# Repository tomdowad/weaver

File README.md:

# weaver
A collection of circuit boards and methods in support of reusable modular electronics

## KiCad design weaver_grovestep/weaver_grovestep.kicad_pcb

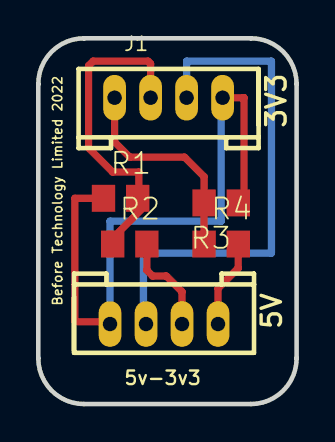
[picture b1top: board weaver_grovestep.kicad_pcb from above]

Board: 2 copper layers, 14.4 x 20.3 mm, 6 parts (0 on the bottom side), 6 nets.

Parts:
J1, J2: 4P-2.0; HW4-2.0
R1, R2, R3, R4: R0805

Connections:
unnamed: J1.2, R1.2, R2.1
unnamed: J1.1, R3.2, R4.1
unnamed: J1.4, J2.4, R1.1, R3.1
unnamed: J1.3, J2.3
unnamed: J2.2, R2.2
unnamed: J2.1, R4.2

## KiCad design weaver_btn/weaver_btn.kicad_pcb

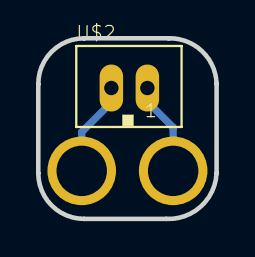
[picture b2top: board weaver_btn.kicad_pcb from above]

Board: 2 copper layers, 9.9 x 10.0 mm, 3 parts (0 on the bottom side), 2 nets.

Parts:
U$1, U$3: BUTTON_PAD
U$2: JST-PH_2-PIN_HEADER; JST_B2B-PH_HEADER

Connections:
unnamed: U$2.P1, U$3.P$1
unnamed: U$1.P$1, U$2.P2

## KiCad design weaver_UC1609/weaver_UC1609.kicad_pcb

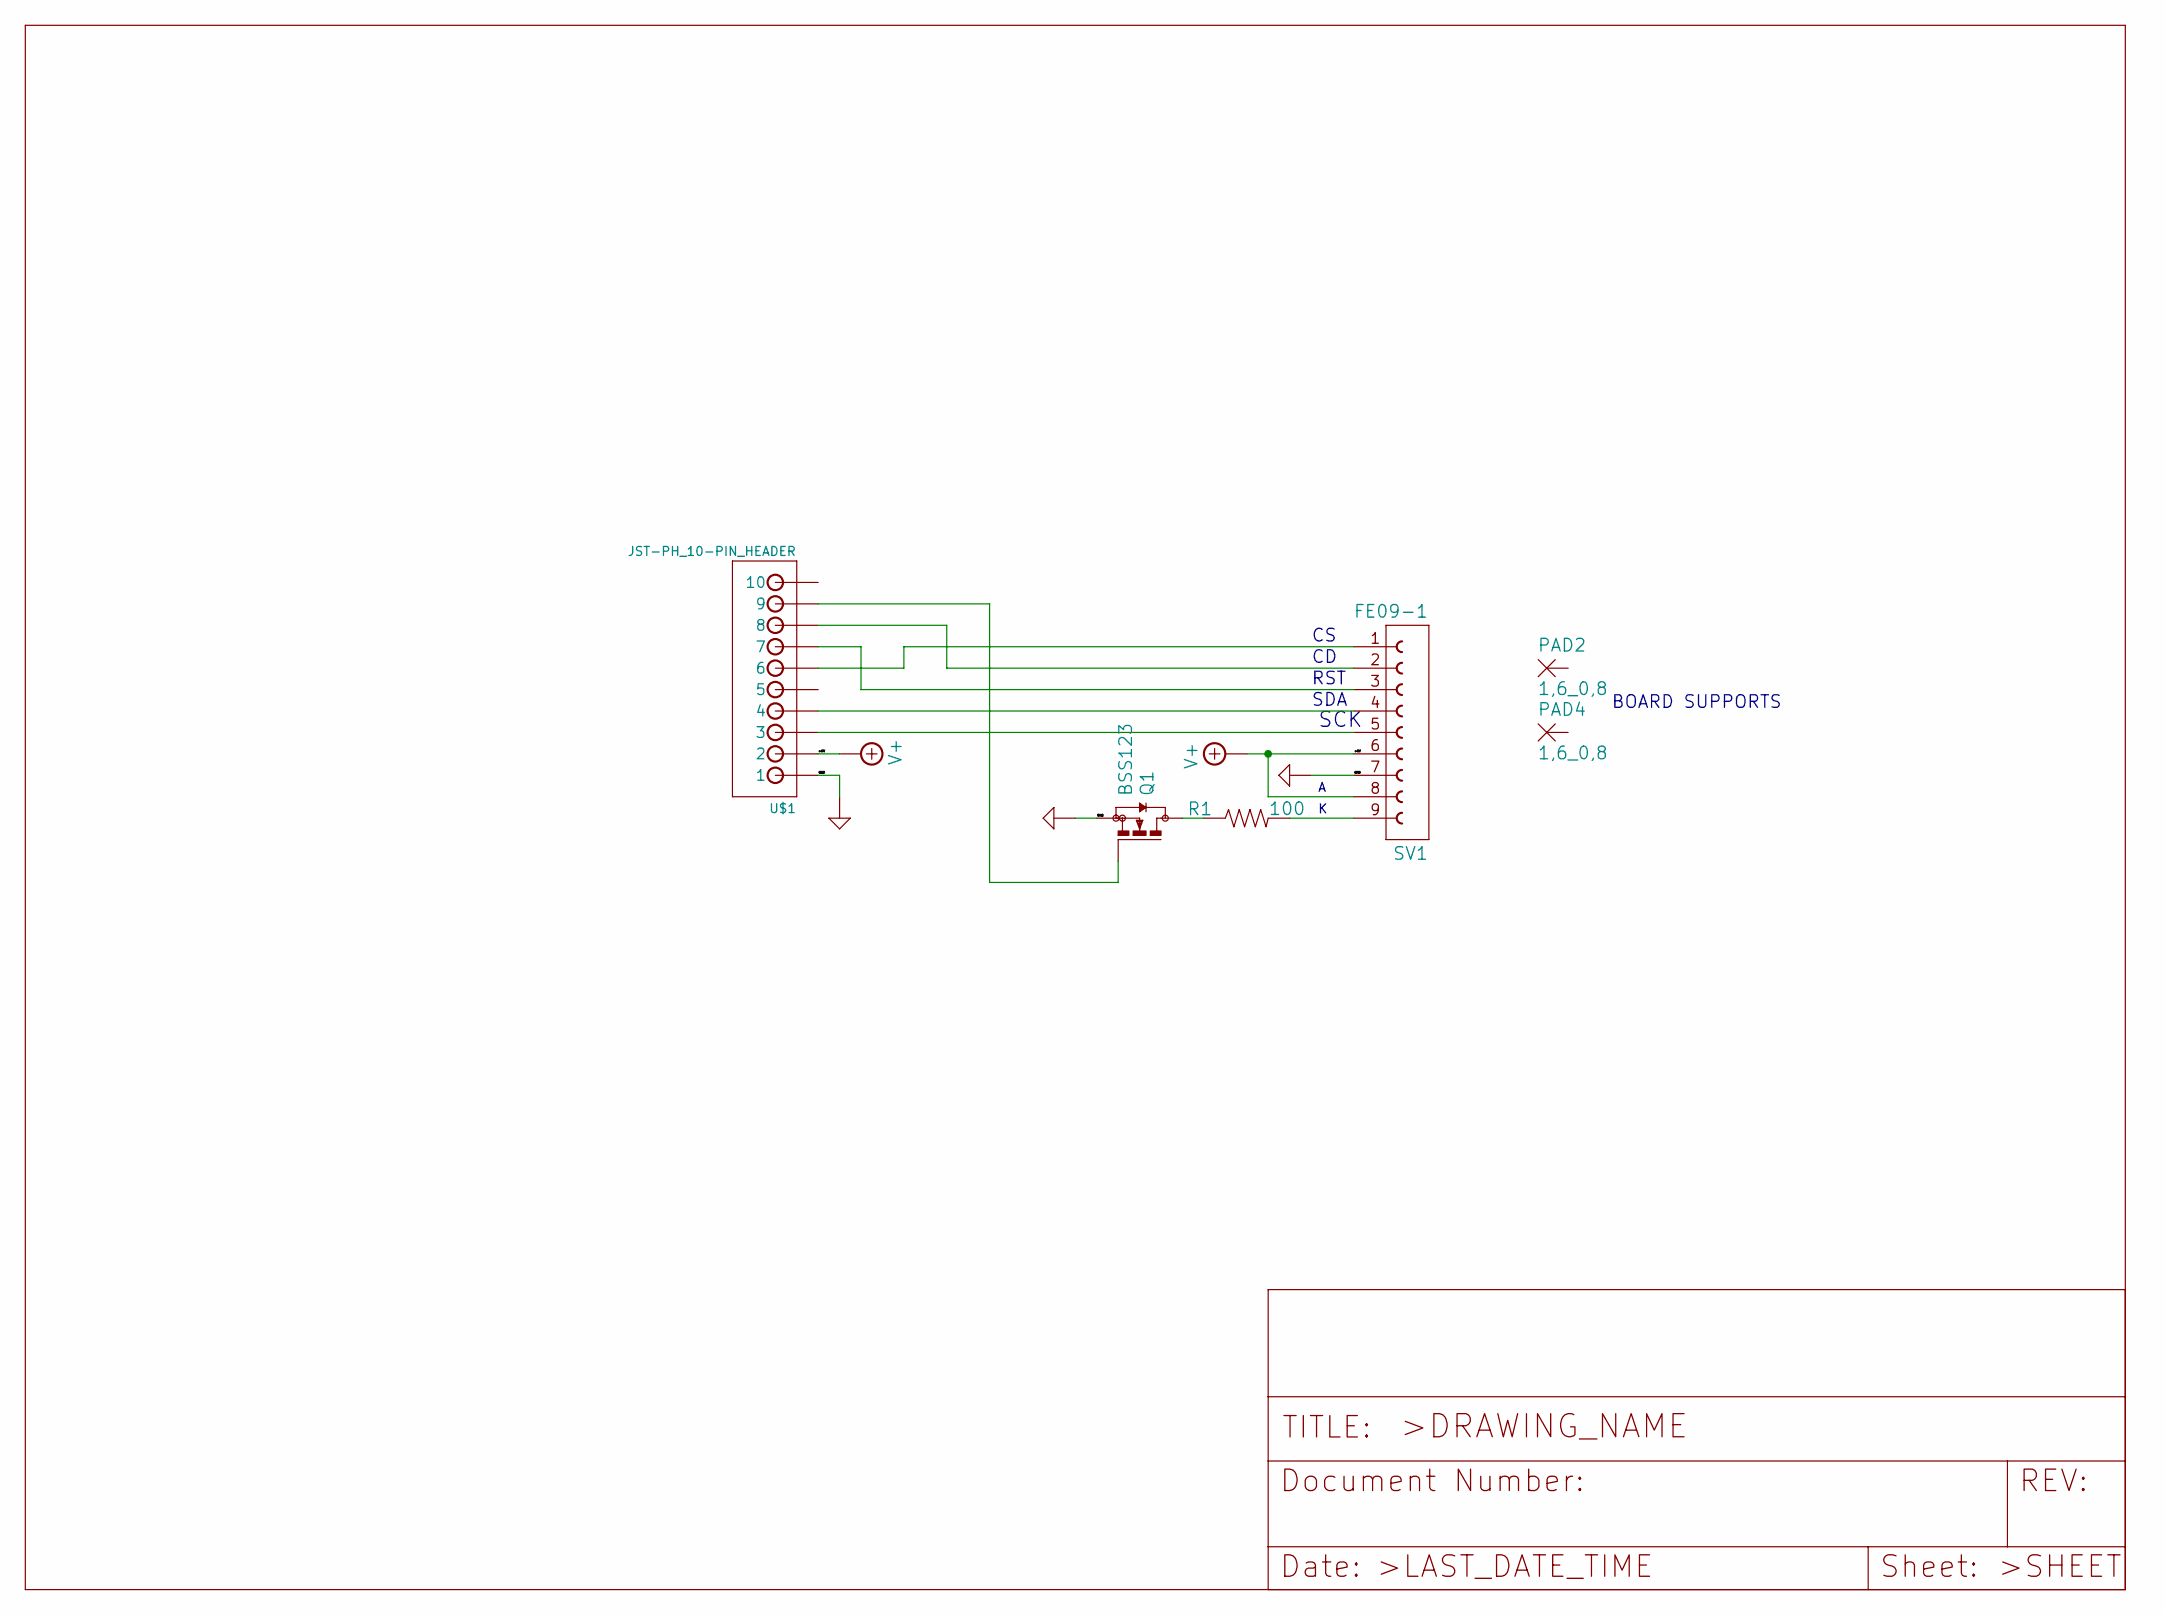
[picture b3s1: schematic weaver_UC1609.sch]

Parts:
PAD2, PAD4: 1,6_0,8
Q1: BSS123; SOT23
R1: 100; M1206
SV1: FE09-1; FE09
U$1: JST-PH_10-PIN_HEADER; JST_B10B-PH_HEADER

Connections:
+5V: SV1.6, SV1.8, U$1.P2 (2)
GND: Q1.2 (S), SV1.7, U$1.P1 (1)
unnamed: Q1.1 (G), U$1.P9 (9)
unnamed: Q1.3 (D), R1.1
unnamed: R1.2, SV1.9
unnamed: SV1.1, U$1.P6 (6)
unnamed: SV1.2, U$1.P8 (8)
unnamed: SV1.3, U$1.P7 (7)
unnamed: SV1.4, U$1.P4 (4)
unnamed: SV1.5, U$1.P3 (3)

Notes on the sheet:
SDA
RST
SCK
BOARD SUPPORTS

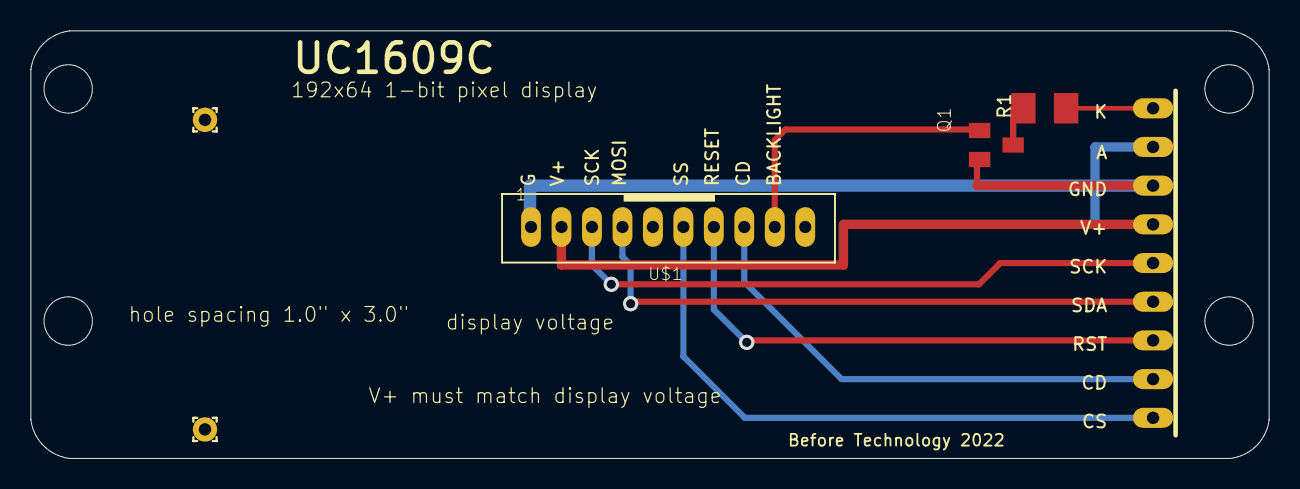
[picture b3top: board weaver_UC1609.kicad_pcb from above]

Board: 2 copper layers, 81.3 x 28.1 mm, 10 parts (1 on the bottom side), 10 nets.

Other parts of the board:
@HOLE0, @HOLE1, @HOLE2, @HOLE3: (no value)

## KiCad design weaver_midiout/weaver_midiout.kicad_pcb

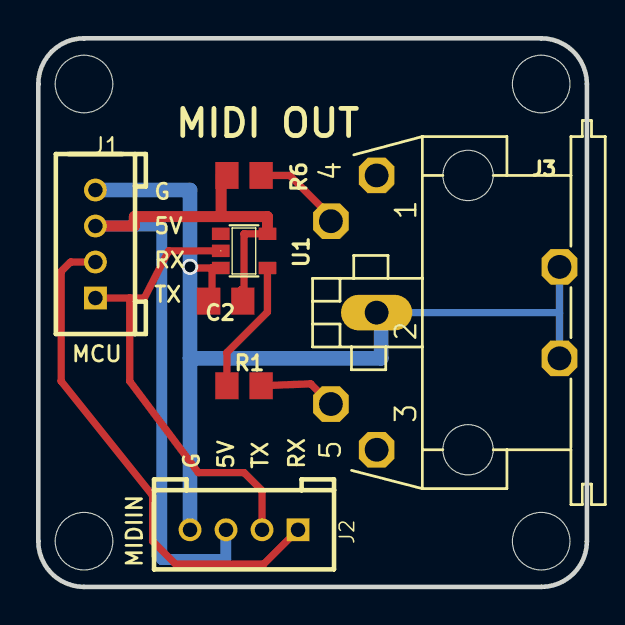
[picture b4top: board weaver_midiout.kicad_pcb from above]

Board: 2 copper layers, 30.5 x 30.5 mm, 11 parts (0 on the bottom side), 7 nets.

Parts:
@HOLE0, @HOLE1, @HOLE2, @HOLE3: (no value)
C2: C0805
J1, J2: 4P-2.0; HW4-2.0
J3: MAB5SH
R1, R6: 220R; R0805
U1: 74LVC1G17DBV; SOT23-5

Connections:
+5V: C2.1, J1.3, J2.3, R6.1, U1.5
GND: C2.2, J1.4, J2.4, J3.2, J3.PE, J3.PE@, U1.3
unnamed: J1.2, J2.1
unnamed: J3.4, R6.2
unnamed: R1.1, U1.4
unnamed: J3.5, R1.2
TX: J1.1, J2.2, U1.2

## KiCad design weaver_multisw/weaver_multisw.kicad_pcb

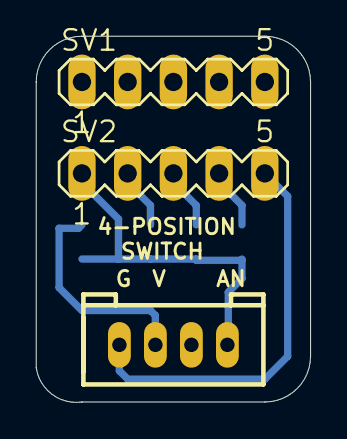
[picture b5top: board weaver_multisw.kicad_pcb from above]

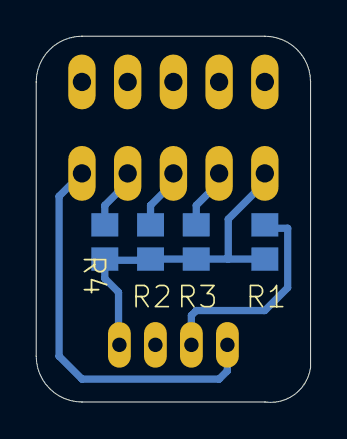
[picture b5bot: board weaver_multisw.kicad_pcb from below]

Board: 2 copper layers, 15.2 x 20.3 mm, 7 parts (4 on the bottom side), 6 nets.

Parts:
J2: 4P-2.0; HW4-2.0
R1: 1k; R0805
R2: 2k2; R0805
R3: 470; R0805
R4: 4.7k; R0805
SV1, SV2: MA05-1

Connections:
GND: J2.4, SV2.5
unnamed: J2.1, R1.1, R2.1, R3.1, R4.1, SV2.1
unnamed: R2.2, SV2.3
unnamed: R3.2, SV2.2
unnamed: R4.2, SV2.4
V+: J2.3, R1.2

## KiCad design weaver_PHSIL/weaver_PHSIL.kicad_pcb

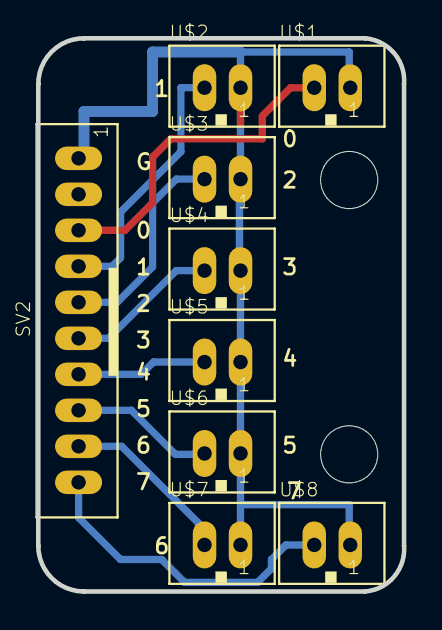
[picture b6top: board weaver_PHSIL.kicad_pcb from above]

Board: 2 copper layers, 20.3 x 30.7 mm, 11 parts (0 on the bottom side), 9 nets.

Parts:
@HOLE0, @HOLE1: (no value)
SV2: JST-PH_10-PIN_HEADER; JST_B10B-PH_HEADER
U$1, U$2, U$3, U$4, U$5, U$6, U$7, U$8: JST-PH_2-PIN_HEADER; JST_B2B-PH_HEADER

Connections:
unnamed: SV2.P1, U$1.P1, U$2.P1, U$3.P1, U$4.P1, U$5.P1, U$6.P1, U$7.P1, U$8.P1
unnamed: SV2.P3, U$1.P2
unnamed: SV2.P4, U$2.P2
unnamed: SV2.P5, U$3.P2
unnamed: SV2.P6, U$4.P2
unnamed: SV2.P7, U$5.P2
unnamed: SV2.P8, U$6.P2
unnamed: SV2.P9, U$7.P2
unnamed: SV2.P10, U$8.P2

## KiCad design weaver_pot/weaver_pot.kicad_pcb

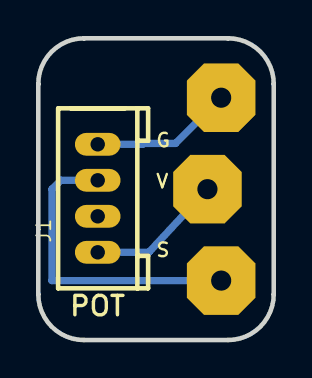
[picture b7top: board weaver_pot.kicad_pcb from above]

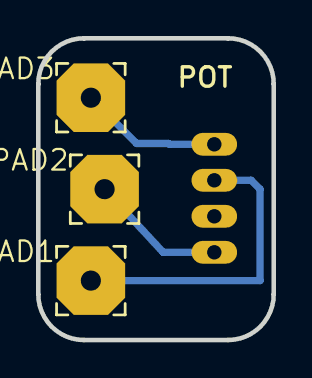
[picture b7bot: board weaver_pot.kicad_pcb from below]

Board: 2 copper layers, 13.1 x 16.8 mm, 4 parts (3 on the bottom side), 3 nets.

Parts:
J1: 4P-2.0; HW4-2.0
PAD1, PAD2, PAD3: 3,81_1,1

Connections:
unnamed: J1.4, PAD3.1
unnamed: J1.3, PAD1.1
unnamed: J1.1, PAD2.1

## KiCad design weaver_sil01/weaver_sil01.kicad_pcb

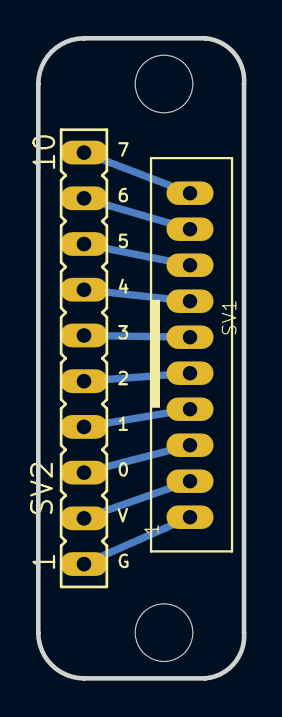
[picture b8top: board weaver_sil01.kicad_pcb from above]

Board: 2 copper layers, 11.4 x 35.6 mm, 4 parts (0 on the bottom side), 10 nets.

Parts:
@HOLE0, @HOLE1: (no value)
SV1: JST-PH_10-PIN_HEADER; JST_B10B-PH_HEADER
SV2: FE10

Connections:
unnamed: SV1.P8, SV2.8
unnamed: SV1.P3, SV2.3
unnamed: SV1.P4, SV2.4
unnamed: SV1.P5, SV2.5
unnamed: SV1.P6, SV2.6
unnamed: SV1.P7, SV2.7
unnamed: SV1.P9, SV2.9
unnamed: SV1.P10, SV2.10
unnamed: SV1.P1, SV2.1
unnamed: SV1.P2, SV2.2

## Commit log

2022-05-11 Create Eagle
